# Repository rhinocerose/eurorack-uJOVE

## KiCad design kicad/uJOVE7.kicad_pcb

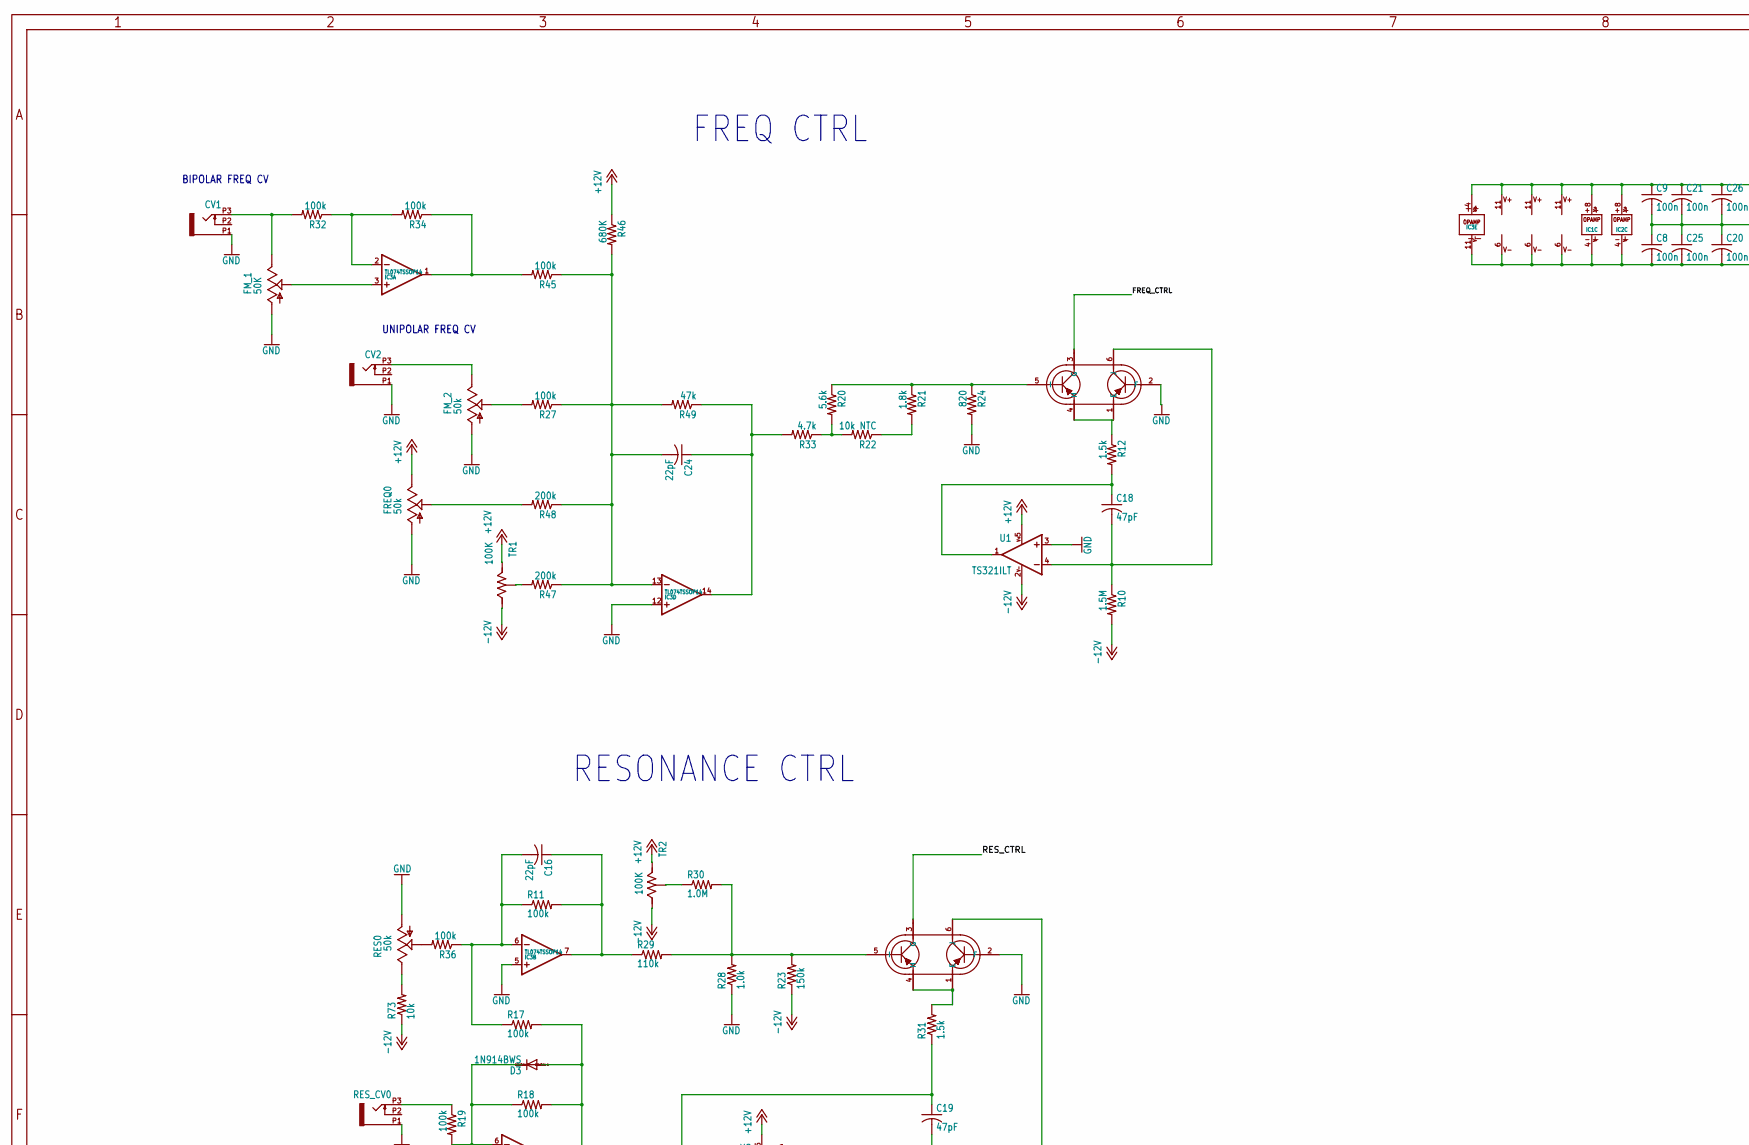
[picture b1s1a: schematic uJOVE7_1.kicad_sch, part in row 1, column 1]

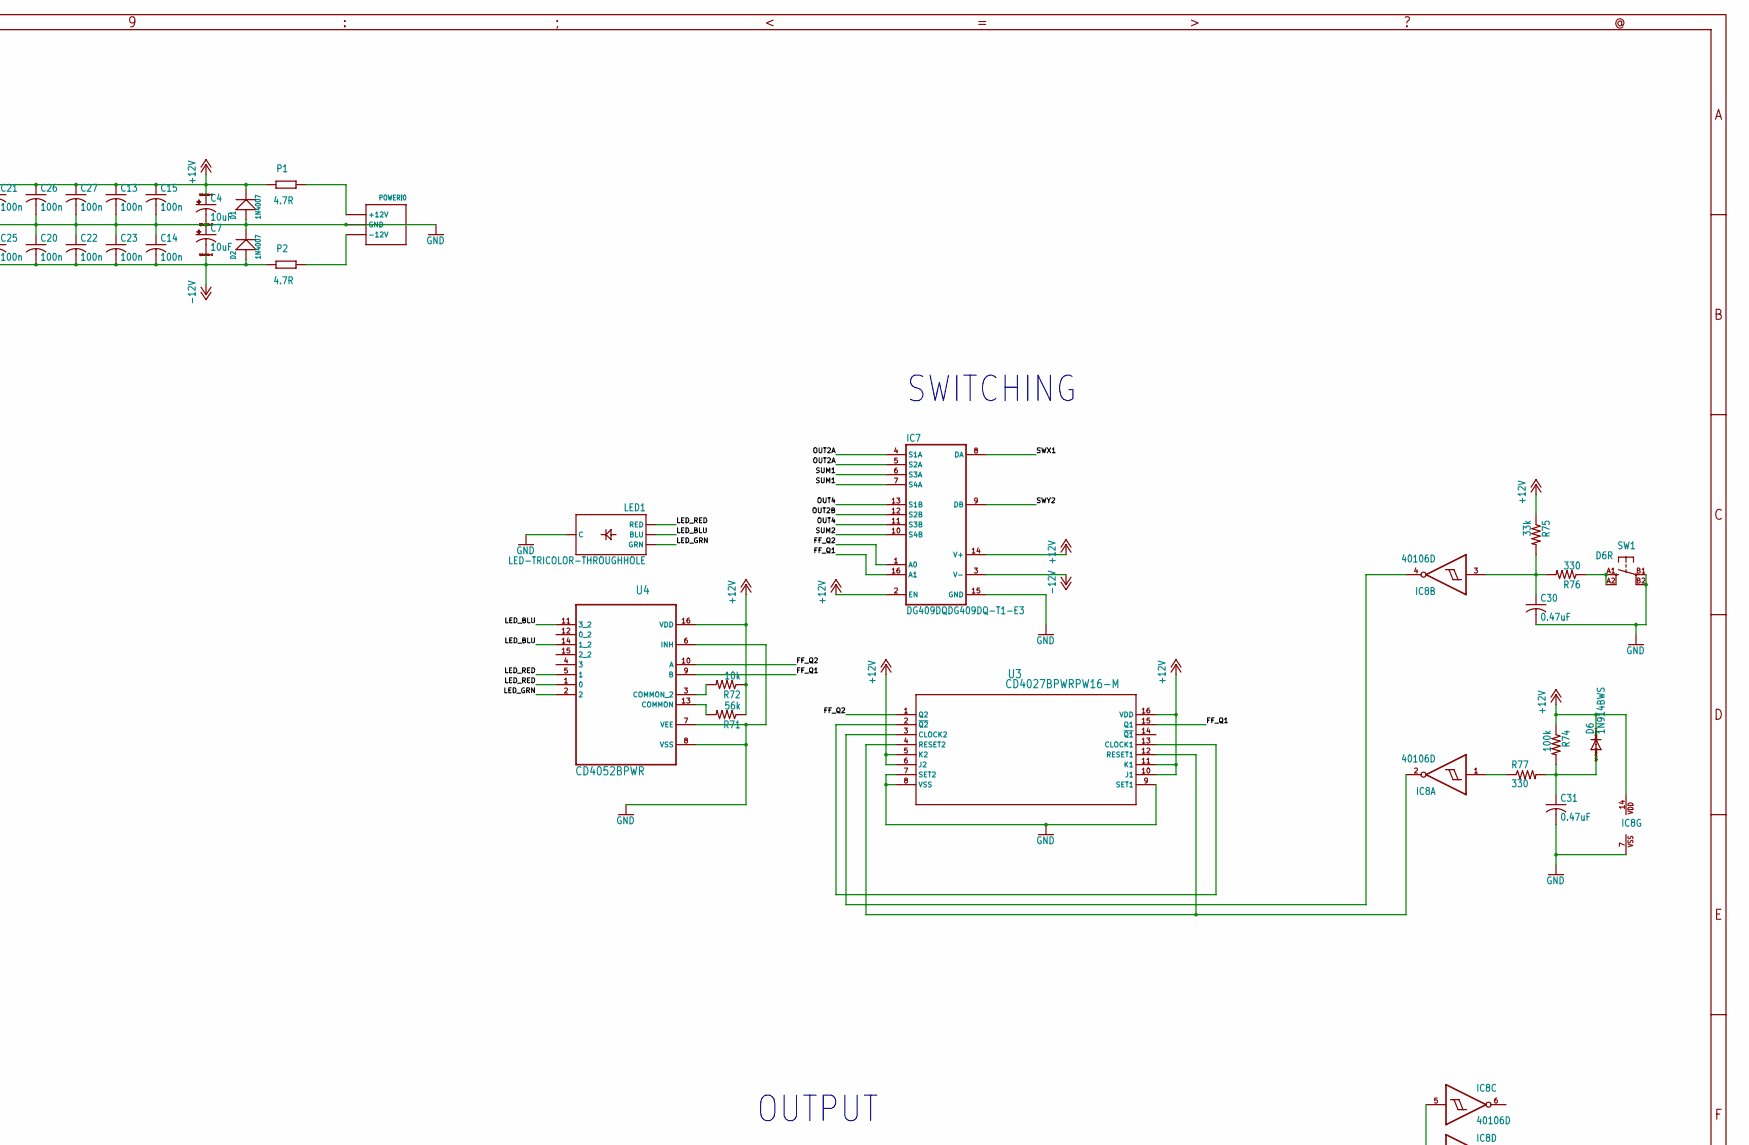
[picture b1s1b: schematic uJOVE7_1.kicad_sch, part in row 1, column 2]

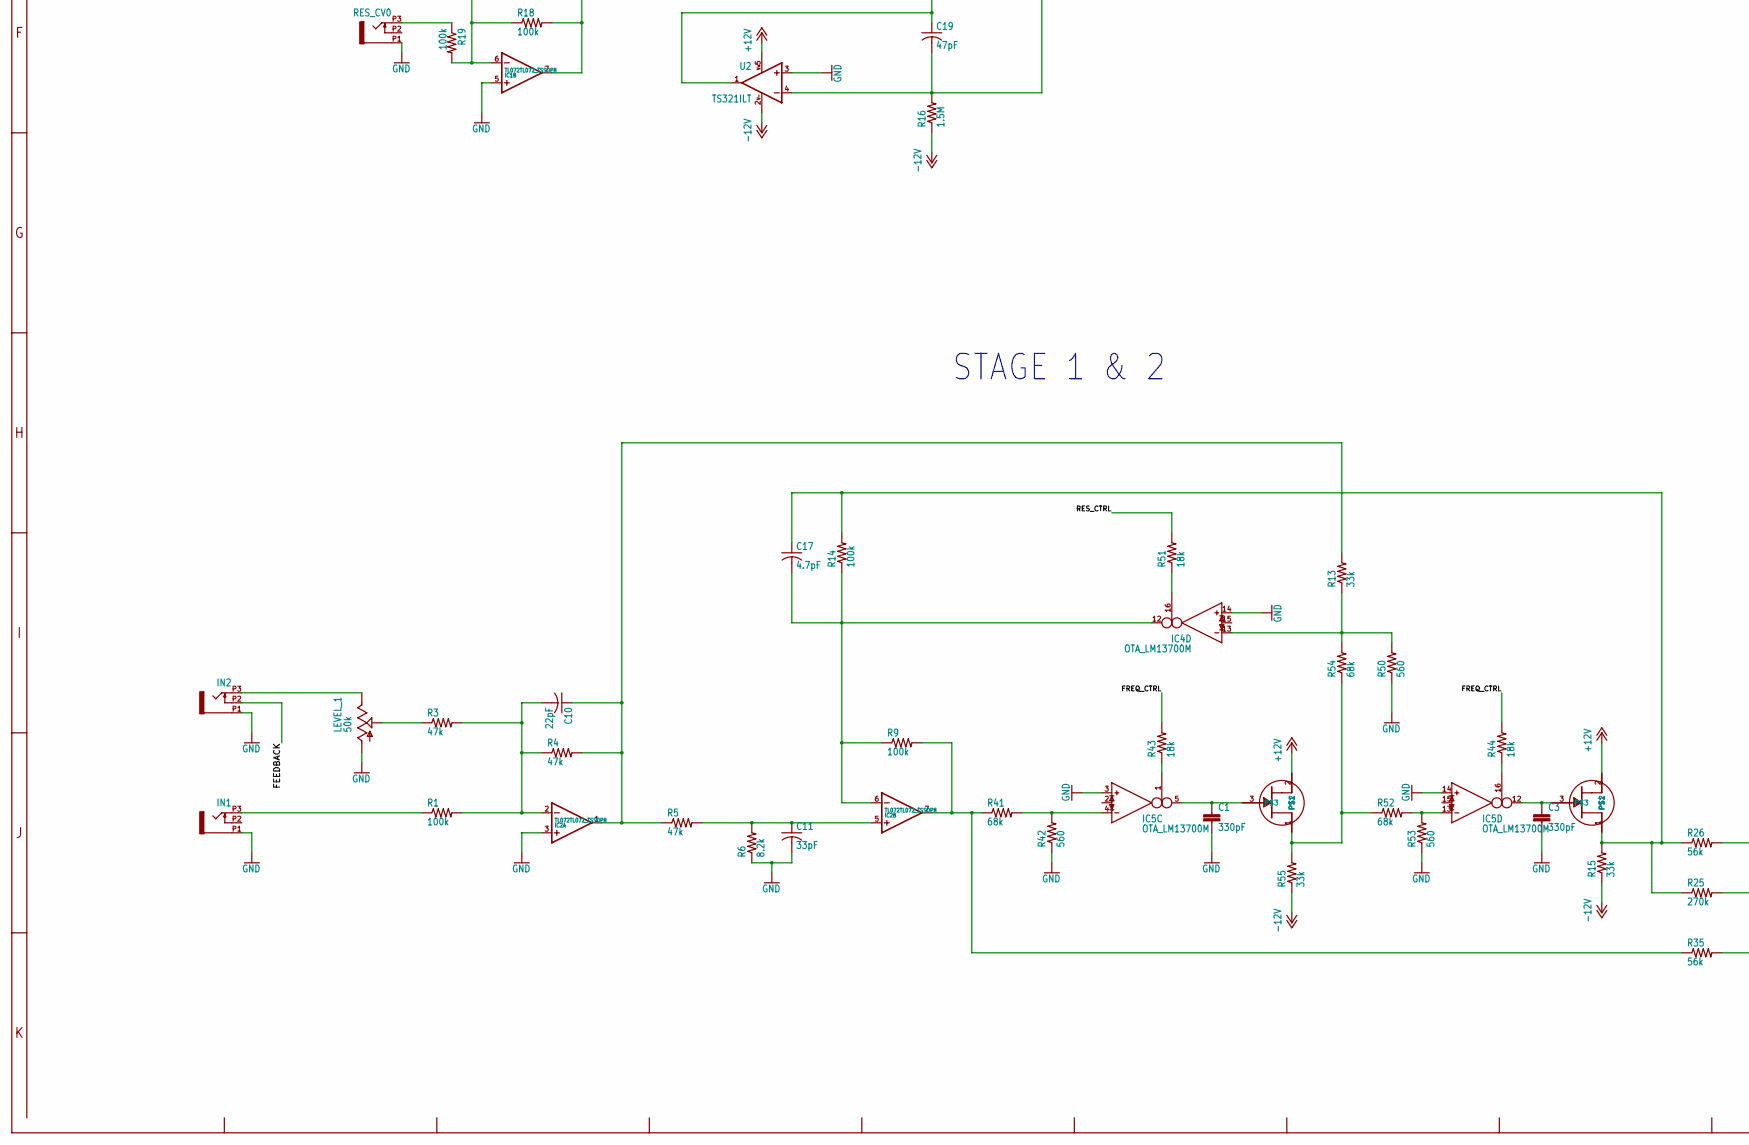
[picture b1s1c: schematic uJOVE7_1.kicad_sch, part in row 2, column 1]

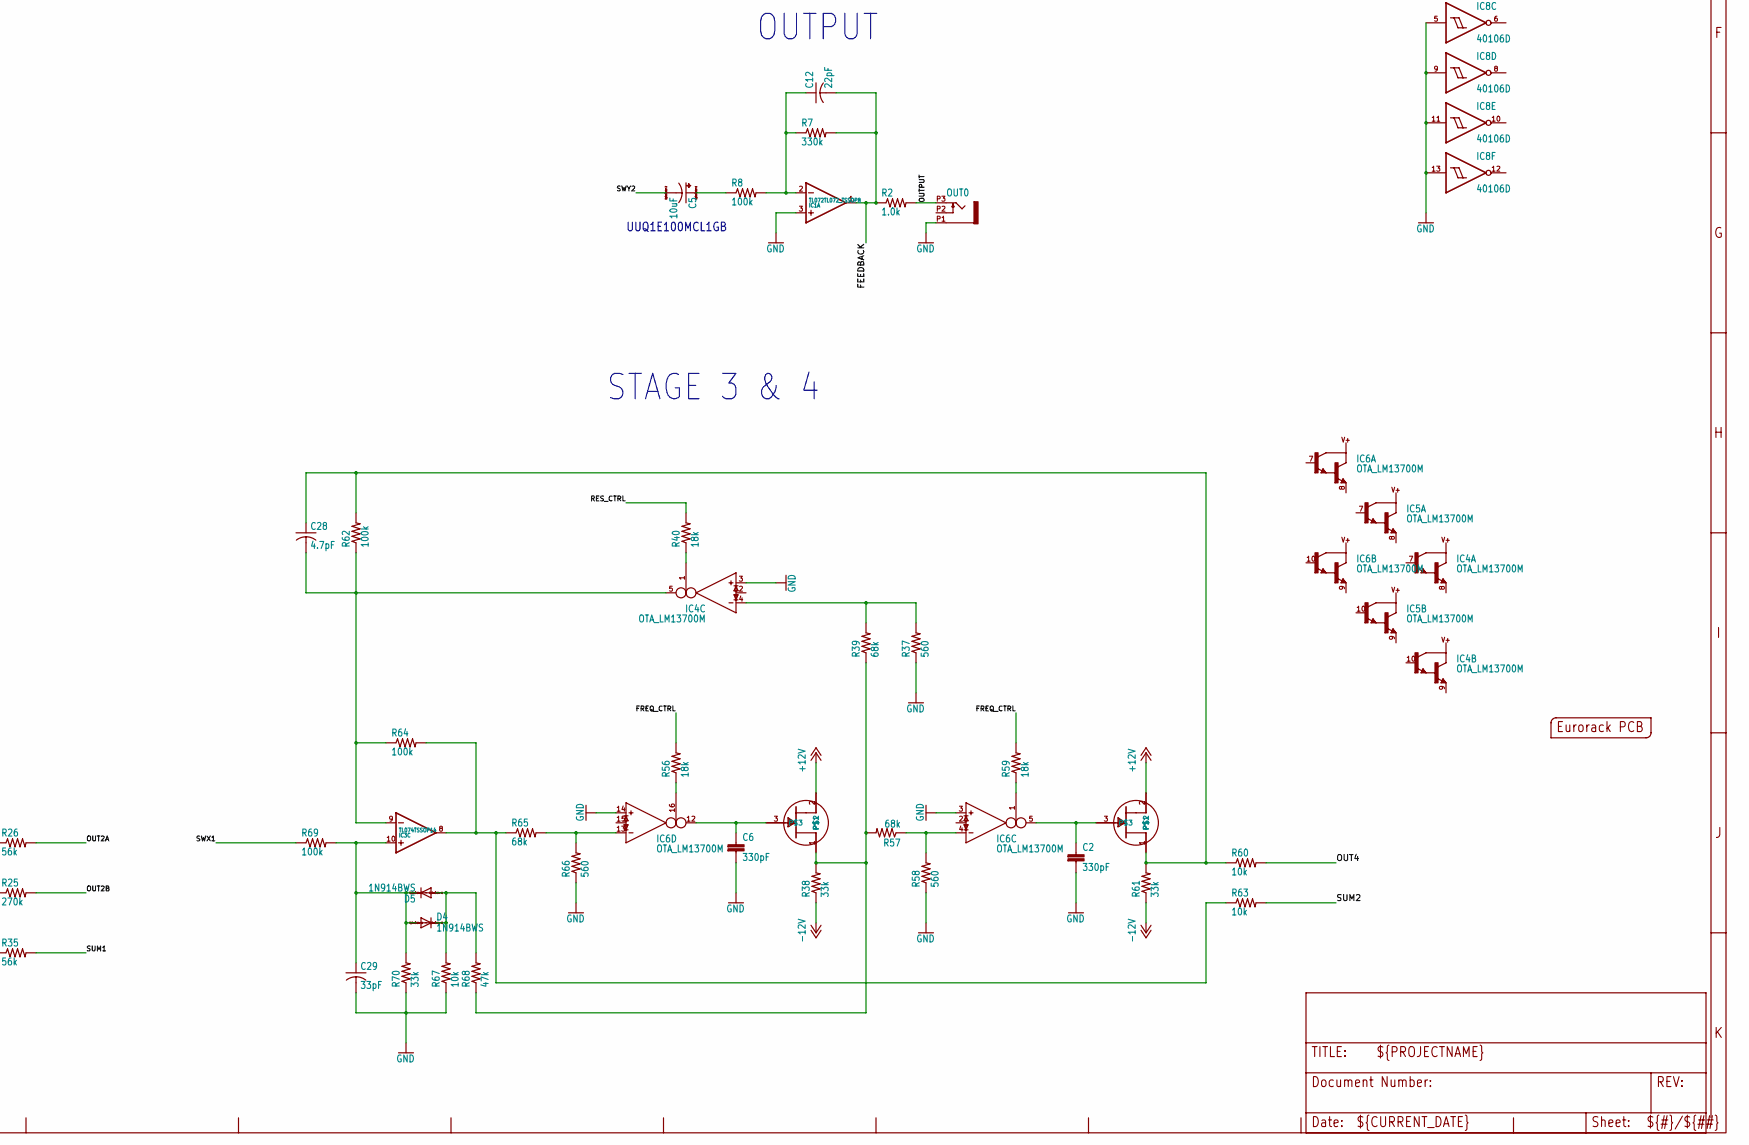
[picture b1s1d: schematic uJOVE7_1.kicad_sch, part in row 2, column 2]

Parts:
C1, C2, C3, C6: 330pF; C5B5
C4, C5, C7: 10uF; PANASONIC_C
C8, C9, C13, C14, C15, C20, C21, C22, C23, C25, C26, C27: 100n; C0603
C10, C12, C16, C24: 22pF; C0603
C11, C29: 33pF; C0603
C17, C28: 4.7pF; C0603
C18, C19: 47pF; C0603
C30, C31: 0.47uF; C0603
CV1, CV2: OG-PJ301_PJ301_THONKICONN; OG-PJ301_WQP_PJ_301M6_NO_HOLE
D1, D2: 1N4007; DO-214AC
D3, D4, D5, D6: 1N914BWS; SOD323-R
FM_1: 50K; OG-POTS_ALPS_POT_VERTICAL
FM_2: 50k; OG-POTS_ALPS_POT_VERTICAL
FREQ0: 50k; OG-POTS_ALPS_POT_VERTICAL_PS
IC1, IC2: TL072TL072_TSSOP8; TL072_TSSOP8
IC3: TL074TSSOP14; TSSOP14
IC4, IC5, IC6: OTA_LM13700M; OTA_SO16
IC7: DG409DQDG409DQ-T1-E3; TSSOP16
IC8: 40106D; SO14
IN1, IN2: OG-PJ301_PJ301_THONKICONN; OG-PJ301_WQP_PJ_301M6_NO_HOLE
LED1: LED-TRICOLOR-THROUGHHOLE
LEVEL_1: 50k; OG-POTS_ALPS_POT_VERTICAL
OUT0: OG-PJ301_PJ301_THONKICONN; OG-PJ301_WQP_PJ_301M6_NO_HOLE
P1, P2: 4.7R; R1206
PCB1: EURORACK_PCB; EURORACK8HPPCB-S
POWER!0: POWER_SIMPLE; 2X05_SMT_HEADER
Q1, Q2: BCM857BS; SOT65P210X110-6N
Q3, Q4, Q5, Q6: MMBFJ112MMBFJ112; SOT23
R1, R8, R9, R11, R14, R17, R18, R19, R27, R32, R34, R36, R45, R62, R64, R69, R74: 100k; R0603
R2, R28: 1.0k; R0603
R3, R4, R5, R49, R68: 47k; R0603
R6: 8.2k; R0603
R7: 330k; R0603
R10, R16: 1.5M; R0603
R12, R31: 1.5k; R0603
R13, R15, R38, R55, R61, R70, R75: 33k; R0603
R20: 5.6k; R0603
R21: 1.8k; R0603
R22: 10k NTC; R0805
R23: 150k; R0603
R24: 820; R0603
R25: 270k; R0603
R26, R35, R71: 56k; R0603
R29: 110k; R0603
R30: 1.0M; R0603
R33: 4.7k; R0603
R37, R42, R50, R53, R58, R66: 560; R0603
R39, R41, R52, R54, R57, R65: 68k; R0603
R40, R43, R44, R51, R56, R59: 18k; R0603
R46: 680K; R0603
R47, R48: 200k; R0603
R60, R63, R67, R72, R73: 10k; R0603
R76, R77: 330; R0603
RES0: 50k; OG-POTS_ALPS_POT_VERTICAL_PS
RES_CV0: OG-PJ301_PJ301_THONKICONN; OG-PJ301_WQP_PJ_301M6_NO_HOLE
SW1: D6R
TR1, TR2: 100K; TC33X-2
U1, U2: TS321ILT; SOT23-5
U3: CD4027BPWRPW16-M; PW16-M
U4: CD4052BPWR; SOP65P640X120-16N

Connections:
+12V: C4.+, C9.1, C13.1, C15.1, C21.1, C26.1, C27.1, D1.2 (-), D6.C, FREQ0.P$1 (E), IC1.8 (V+), IC2.8 (V+), IC3.4 (V+), IC4.11 (V+), IC5.11 (V+), IC6.11 (V+), IC7.2 (EN), IC7.14 (V+), IC8.14 (VDD), P1.1, Q3.2, Q4.2, Q5.2, Q6.2, R46.1, R71.1, R72.1, R74.1, R75.1, TR1.1, TR2.1, U1.5 (V+), U2.5 (V+), U3.5 (K2), U3.6 (J2), U3.10 (J1), U3.11 (K1), U3.16 (VDD), U4.16 (VDD)
-12V: C7.-, C8.2, C14.2, C20.2, C22.2, C23.2, C25.2, D2.1 (+), IC1.4 (V-), IC2.4 (V-), IC3.11 (V-), IC4.6 (V-), IC5.6 (V-), IC6.6 (V-), IC7.3 (V-), P2.1, R10.2, R15.1, R16.1, R23.1, R38.1, R55.1, R61.1, R73.1, TR1.3, TR2.3, U1.2 (V-), U2.2 (V-)
FEEDBACK: C12.2, IC1.1 (OUT), IN2.P2 (2), R2.1, R7.2
FF_Q1: IC7.16 (A1), U3.15 (Q1), U4.9 (B)
FF_Q2: IC7.1 (A0), U3.1 (Q2), U4.10 (A)
FREQ_CTRL: Q1.3 (G), R43.2, R44.2, R56.2, R59.2
GND: C1.2, C2.2, C3.2, C4.-, C6.2, C7.+, C8.1, C9.2, C11.2, C13.2, C14.1, C15.2, C20.1, C21.2, C22.1, C23.1, C25.1, C26.2, C27.2, C29.2, C30.2, C31.2, CV1.P1 (1), CV2.P1 (1), D1.1 (+), D2.2 (-), FM_1.P$3 (A), FM_2.P$3 (A), FREQ0.P$3 (A), IC1.3 (+IN), IC1.5 (+IN), IC2.3 (+IN), IC3.5 (+IN), IC3.12 (+IN), IC4.3 (IN_P), IC4.14 (IN_P), IC5.3 (IN_P), IC5.14 (IN_P), IC6.3 (IN_P), IC6.14 (IN_P), IC7.15 (GND), IC8.5 (I), IC8.7 (VSS), IC8.9 (I), IC8.11 (I), IC8.13 (I), IN1.P1 (1), IN2.P1 (1), LED1.GND (C), LEVEL_1.P$3 (A), OUT0.P1 (1), POWER!0.3 (GND), POWER!0.4 (GND), POWER!0.5 (GND), POWER!0.6 (GND), POWER!0.7 (GND), POWER!0.8 (GND), Q1.2 (F), Q2.2 (F), R6.1, R24.2, R28.1, R37.1, R42.1, R50.1, R53.1, R58.1, R66.1, R67.1, R70.1, RES0.P$3 (A), RES_CV0.P1 (1), SW1.B1, SW1.B2 (P1), U1.3 (+IN), U2.3 (+IN), U3.7 (SET2), U3.8 (VSS), U3.9 (SET1), U4.6 (INH), U4.7 (VEE), U4.8 (VSS)
LED_BLU: LED1.BLU, U4.11 (3_2), U4.14 (1_2)
LED_GRN: LED1.GRN, U4.2
LED_RED: LED1.RED, U4.1 (0), U4.5 (1)
unnamed: P1.2, POWER!0.9 (+12V), POWER!0.10 (+12V)
unnamed: P2.2, POWER!0.1 (-12V), POWER!0.2 (-12V)
unnamed: IN1.P3 (3), R1.1
unnamed: C10.2, IC2.2 (-IN), R1.2, R3.2, R4.1
unnamed: IN2.P3 (3), LEVEL_1.P$1 (E)
unnamed: LEVEL_1.P$2 (S), R3.1
unnamed: C10.1, IC2.1 (OUT), R4.2, R5.1, R13.2
unnamed: C11.1, IC2.5 (+IN), R5.2, R6.2
unnamed: IC2.7 (OUT), R9.2, R35.1, R41.1
unnamed: C17.2, IC2.6 (-IN), IC4.12 (OUT), R9.1, R14.1
unnamed: IC5.4 (IN_N), R41.2, R42.2
unnamed: IC5.1 (I_BIAS), R43.1
unnamed: C1.1, IC5.5 (OUT), Q4.3
unnamed: IC5.13 (IN_N), R52.2, R53.2
unnamed: IC4.13 (IN_N), R13.1, R50.2, R54.2
unnamed: IC4.16 (I_BIAS), R51.1
unnamed: C17.1, Q3.1, R14.2, R15.2, R25.1, R26.1
unnamed: Q4.1, R52.1, R54.1, R55.2
unnamed: IC5.16 (I_BIAS), R44.1
unnamed: R73.2, RES0.P$1 (E)
unnamed: C3.1, IC5.12 (OUT), Q3.3
unnamed: C5.+, R8.1
unnamed: C12.1, IC1.2 (-IN), R7.1, R8.2
unnamed: C31.1, D6.A, R74.2, R77.2
unnamed: IC3.8 (OUT), R63.1, R64.2, R65.1
unnamed: IC6.4 (IN_N), R57.1, R58.2
unnamed: D4.C, D5.A, R67.2, R68.2
unnamed: C29.1, D4.A, D5.C, IC3.10 (+IN), R69.2, R70.2
unnamed: IC6.13 (IN_N), R65.2, R66.2
unnamed: IC4.4 (IN_N), R37.2, R39.2
unnamed: IC6.16 (I_BIAS), R56.1
unnamed: C6.1, IC6.12 (OUT), Q6.3
unnamed: Q6.1, R38.2, R39.1, R57.2, R68.1
unnamed: IC4.1 (I_BIAS), R40.1
unnamed: C28.2, IC3.9 (-IN), IC4.5 (OUT), R62.1, R64.1
unnamed: R36.2, RES0.P$2 (S)
unnamed: IC6.1 (I_BIAS), R59.1
unnamed: C28.1, Q5.1, R60.1, R61.2, R62.2
unnamed: C2.1, IC6.5 (OUT), Q5.3
unnamed: R19.1, RES_CV0.P3 (3)
unnamed: D3.C, IC1.6 (-IN), R18.1, R19.2
unnamed: D3.A, IC1.7 (OUT), R17.2, R18.2
unnamed: C16.2, IC3.6 (-IN), R11.1, R17.1, R36.1
unnamed: R30.1, TR2.2
unnamed: C16.1, IC3.7 (OUT), R11.2, R29.1
unnamed: Q2.5 (I), R23.2, R28.2, R29.2, R30.2
unnamed: Q2.1 (E), Q2.4 (H), R31.2
unnamed: C19.2, Q2.6 (J), R16.2, U2.4 (-IN)
unnamed: C19.1, R31.1, U2.1 (OUT)
unnamed: CV1.P3 (3), FM_1.P$1 (E), R32.2
unnamed: IC3.2 (-IN), R32.1, R34.2
unnamed: FM_1.P$2 (S), IC3.3 (+IN)
unnamed: IC3.1 (OUT), R34.1, R45.2
unnamed: C24.2, IC3.13 (-IN), R27.1, R45.1, R46.2, R47.1, R48.1, R49.2
unnamed: CV2.P3 (3), FM_2.P$1 (E)
unnamed: FM_2.P$2 (S), R27.2
unnamed: FREQ0.P$2 (S), R48.2
unnamed: R47.2, TR1.2
unnamed: C24.1, IC3.14 (OUT), R33.2, R49.1
unnamed: R20.2, R22.2, R33.1
unnamed: Q1.5 (I), R20.1, R21.1, R24.1
unnamed: R21.2, R22.1
unnamed: C18.2, Q1.6 (J), R10.1, U1.4 (-IN)
unnamed: C18.1, R12.2, U1.1 (OUT)
unnamed: IC8.1 (I), R77.1
unnamed: C30.1, IC8.3 (I), R75.2, R76.2
unnamed: IC8.2 (O), U3.4 (RESET2), U3.12 (RESET1)
unnamed: IC8.4 (O), U3.3 (CLOCK2)
unnamed: R76.1, SW1.A1 (S), SW1.A2 (S1)
unnamed: U3.2 (~Q2), U3.13 (CLOCK1)
unnamed: R72.2, U4.3 (COMMON_2)
unnamed: R71.2, U4.13 (COMMON)
OUT2A: IC7.4 (S1A), IC7.5 (S2A), R26.2
OUT2B: IC7.12 (S2B), R25.2
OUT4: IC7.11 (S3B), IC7.13 (S1B), R60.2
OUTPUT: OUT0.P3 (3), R2.2
RES_CTRL: Q2.3 (G), R40.2, R51.2
SUM1: IC7.6 (S3A), IC7.7 (S4A), R35.2
SUM2: IC7.10 (S4B), R63.2
SWX1: IC7.8 (DA), R69.1
SWY2: C5.-, IC7.9 (DB)

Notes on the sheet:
BIPOLAR FREQ CV
UNIPOLAR FREQ CV
FREQ CTRL
RESONANCE CTRL
STAGE 1 & 2
STAGE 3 & 4
UUQ1E100MCL1GB
OUTPUT
SWITCHING

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
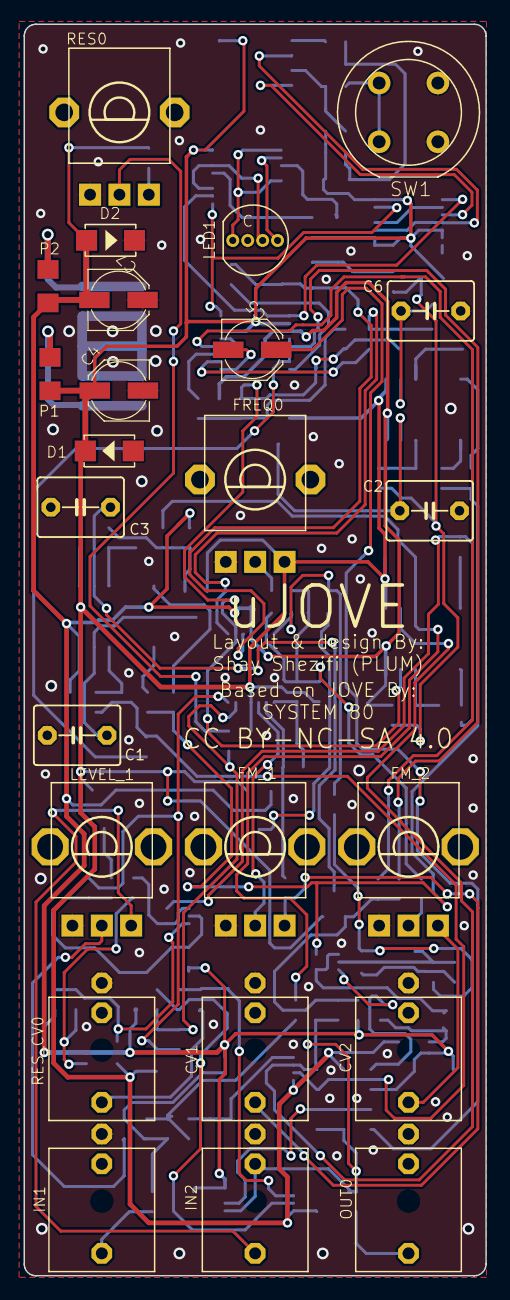
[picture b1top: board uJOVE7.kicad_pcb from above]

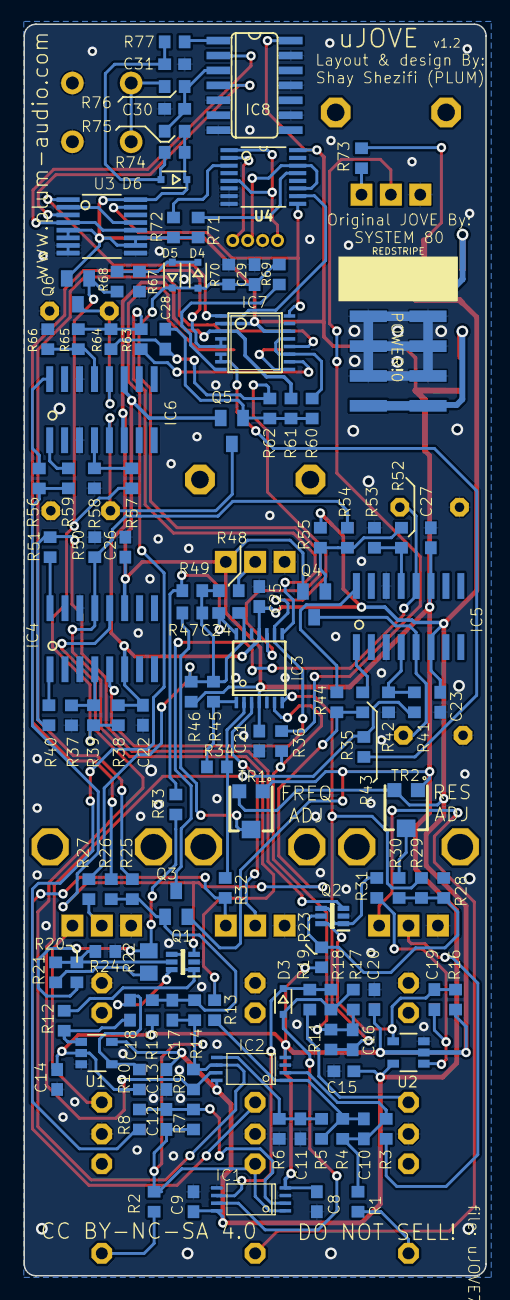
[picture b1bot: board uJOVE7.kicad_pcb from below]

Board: 2 copper layers, 39.3 x 106.5 mm, 151 parts (126 on the bottom side), 92 nets.

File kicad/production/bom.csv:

Designator,Footprint,Quantity,Value,LCSC Part #
"C1, C2, C3, C6",C5B5_116,4,330pF,
"C10, C12, C16, C24",C0603_348,4,22pF,
"C11, C29",C0603_348,2,33pF,
"C13, C14, C15, C20, C21, C22, C23, C25, C26, C27, C8, C9",C0603_348,12,100n,
"C17, C28",C0603_348,2,4.7pF,
"C18, C19",C0603_348,2,47pF,
"C30, C31",C0603_348,2,0.47uF,
"C4, C5, C7",PANASONIC_C_348,3,10uF,
"CV1, CV2, IN1, IN2, OUT0, RES_CV0",OG-PJ301_WQP_PJ_301M6_NO_HOLE,6,OG-PJ301_PJ301_THONKICONN,
"D1, D2",DO-214AC_467,2,1N4007,
"D3, D4, D5, D6",SOD323-R_210,4,1N914BWS,
"FM_1, FM_2, LEVEL_1",OG-POTS_ALPS_POT_VERTICAL,3,50K,
"FREQ0, RES0",OG-POTS_ALPS_POT_VERTICAL_PS,2,50k,
"IC1, IC2",TL072_TSSOP8,2,TL072TL072_TSSOP8,
IC3,TSSOP14,1,TL074TSSOP14,
"IC4, IC5, IC6",OTA_SO16,3,OTA_LM13700M,
IC7,TSSOP16,1,DG409DQDG409DQ-T1-E3,
IC8,SO14_80,1,40106D,
LED1,LED-TRICOLOR-THROUGHHOLE,1,LED-TRICOLOR-THROUGHHOLE,
"P1, P2",R1206_334,2,4.7R,
PCB1,EURORACK8HPPCB-S,1,EURORACK_PCB,
POWER!0,2X05_SMT_HEADER,1,POWER_SIMPLE,
"Q1, Q2",SOT65P210X110-6N,2,BCM857BS,
"Q3, Q4, Q5, Q6",SOT23,4,MMBFJ112MMBFJ112,
"R1, R11, R14, R17, R18, R19, R27, R32, R34, R36, R45, R62, R64, R69, R74, R8, R9",R0603_334,17,100k,
"R10, R16",R0603_334,2,1.5M,
"R12, R31",R0603_334,2,1.5k,
"R13, R15, R38, R55, R61, R70, R75",R0603_334,7,33k,
"R2, R28",R0603_334,2,1.0k,
R20,R0603_334,1,5.6k,
R21,R0603_334,1,1.8k,
R22,R0805_348,1,10k NTC,
R23,R0603_334,1,150k,
R24,R0603_334,1,820,
R25,R0603_334,1,270k,
"R26, R35, R71",R0603_334,3,56k,
R29,R0603_334,1,110k,
"R3, R4, R49, R5, R68",R0603_334,5,47k,
R30,R0603_334,1,1.0M,
R33,R0603_334,1,4.7k,
"R37, R42, R50, R53, R58, R66",R0603_334,6,560,
"R39, R41, R52, R54, R57, R65",R0603_334,6,68k,
"R40, R43, R44, R51, R56, R59",R0603_334,6,18k,
R46,R0603_334,1,680K,
"R47, R48",R0603_334,2,200k,
R6,R0603_334,1,8.2k,
"R60, R63, R67, R72, R73",R0603_334,5,10k,
R7,R0603_334,1,330k,
"R76, R77",R0603_334,2,330,
SW1,D6R,1,D6R,
"TR1, TR2",TC33X-2,2,100K,
"U1, U2",SOT23-5,2,TS321ILT,
U3,PW16-M,1,CD4027BPWRPW16-M,
U4,SOP65P640X120-16N,1,CD4052BPWR,

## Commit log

2025-08-07 Kicad

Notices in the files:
kicad/uJOVE7.kicad_pcb:
CC BY-NC-SA 4.0
